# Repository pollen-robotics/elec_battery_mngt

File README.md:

# Battery-related Electronic Boards

This repository gathers several small PCBs for battery management. Including:

 - 2S BMS + USB-ish charger

## Basically
 - Designed with KiCAD 9.

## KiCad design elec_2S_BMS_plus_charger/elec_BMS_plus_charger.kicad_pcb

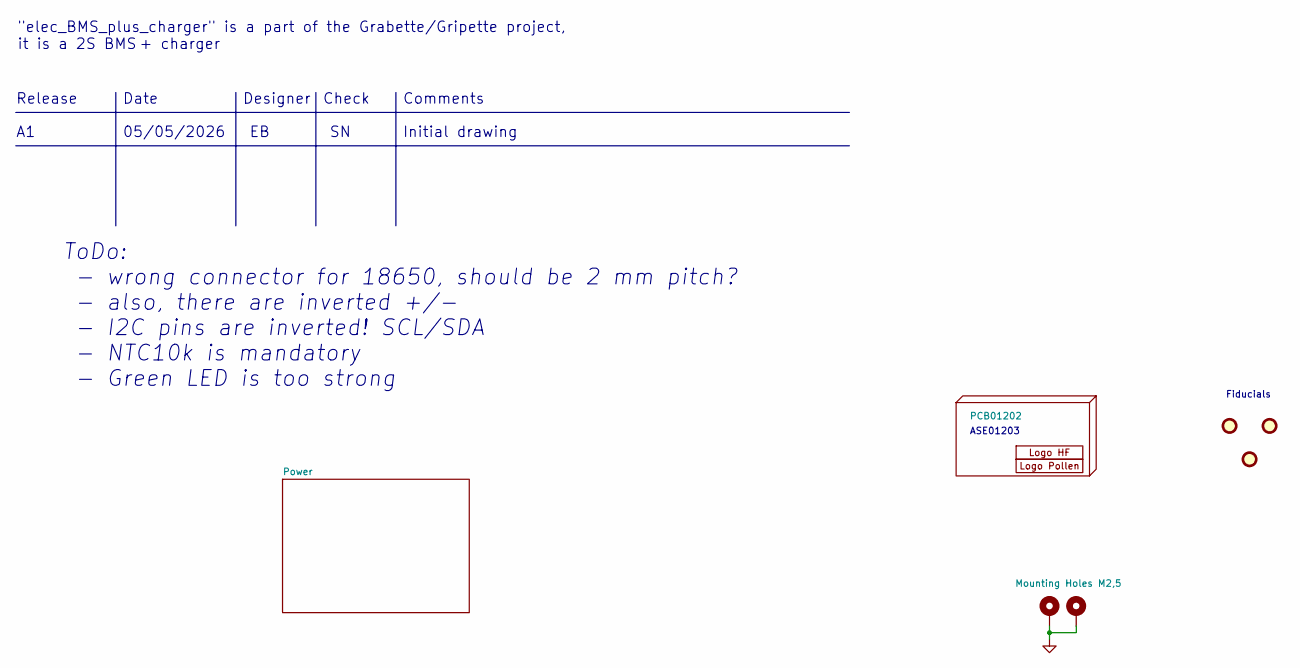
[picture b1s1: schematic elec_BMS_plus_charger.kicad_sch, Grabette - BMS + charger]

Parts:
FID1, FID2, FID3: DNP Fiducial; Fiducial_1mm_Mask2mm
H1: PCB01202
H2: Logo HF 2025; Logo_HF_2025
H3: DNP Logo Pollen 2021; Logo_Pollen_2021_sq
H4, H5: Mounting Holes M2,5; MountingHole_2.7mm_M2.5_ISO7380_Pad_TopBottom

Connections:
GND: H4.1, H5.1; also elsewhere on the board

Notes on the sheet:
Date
Check
Release
Fiducials
ASE01203
ToDo: - wrong connector for 18650, should be 2 mm pitch? - also, there are inverted +/- - I2C pins are inverted! SCL/SDA - NTC10k is mandatory - Green LED is too strong
Initial drawing
"elec_BMS_plus_charger" is a part of the Grabette/Gripette project, it is a 2S BMS + charger
Designer
Comments
05/05/2026

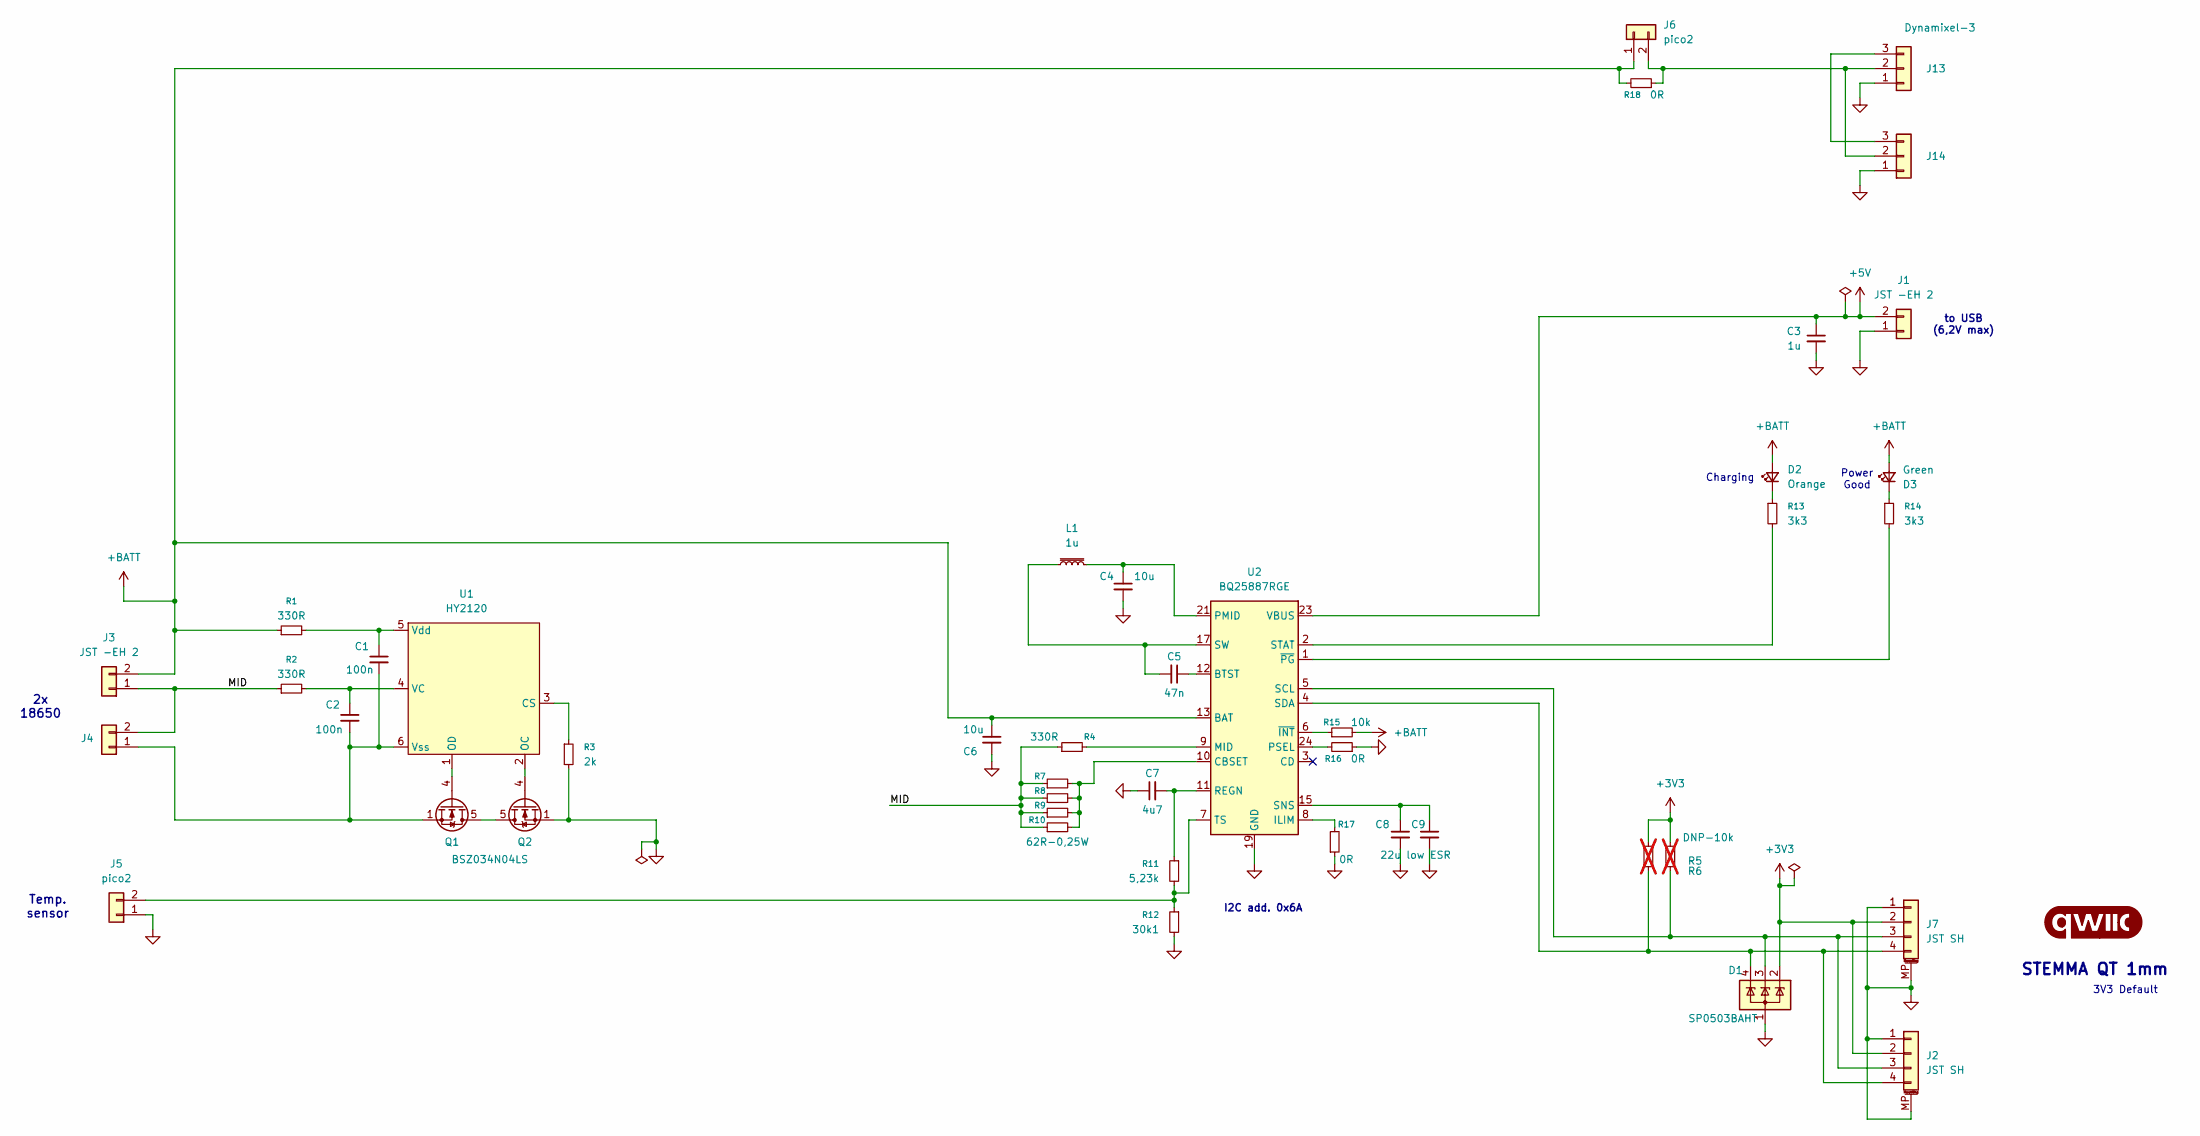
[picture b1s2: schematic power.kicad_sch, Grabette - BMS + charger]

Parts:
C1, C2: 100n; C_0402_1005Metric; LCSC Part C1525
C3: 1u; C_0402_1005Metric; LCSC Part C52923
C4, C6: 10u; C_0603_1608Metric; LCSC Part C19702
C5: 47n; C_0402_1005Metric; LCSC Part C272875
C7: 4u7; C_0603_1608Metric; LCSC Part C1705
C8, C9: 22u low ESR; C_0805_2012Metric; LCSC Part C5674
D1: SP0503BAHT; SOT-143; LCSC Part C41364459
D2: Orange; LED_0603_1608Metric; LCSC Part C84269
D3: Green; LED_0603_1608Metric; LCSC Part C19171301
G1: qwiic_Logo; Logo_qwiic_5mm
J1, J3, J4: JST -EH 2; JST_EH_B2B-EH-A_1x02_P2.50mm_Vertical; LCSC Part C160262
J2, J7: JST SH; JST_SH_BM04B-SRSS-TB_1x04-1MP_P1.00mm_Vertical; LCSC Part C160390
J5, J6: pico2; Molex_PicoBlade_53047-0210_1x02_P1.25mm_Vertical; LCSC Part C114130
J13, J14: Dynamixel-3; JST_EH_B3B-EH-A_1x03_P2.50mm_Vertical; LCSC Part C160259
L1: 1u; IND-SMD_L7.2-W6.6_GPSR0730; LCSC Part C5189744
Q1, Q2: BSZ034N04LS; PQFN_3.3x3.3mm_-_PG-TDSON-8_FL; LCSC Part C534652
R1, R2, R4: 330R; R_0402_1005Metric; LCSC Part C25104
R3: 2k; R_0402_1005Metric; LCSC Part C2909344
R5, R6: DNP-10k; R_0402_1005Metric; not fitted
R7, R8, R9, R10: 62R-0,25W; R_1206_3216Metric; LCSC Part C3013271
R11: 5,23k; R_0402_1005Metric; LCSC Part C2933105
R12: 30k1; R_0402_1005Metric; LCSC Part C2998131
R13, R14: 3k3; R_0402_1005Metric; LCSC Part C25890
R15: 10k; R_0402_1005Metric; LCSC Part C2906861
R16, R17: 0R; R_0402_1005Metric; LCSC Part C17168
R18: 0R; R_0603_1608Metric; LCSC Part C21189
U1: HY2120; SOT-23-6; LCSC Part C168778
U2: BQ25887RGE; Texas_RGE0024H_VQFN-24-1EP_4x4mm_P0.5mm_EP2.7x2.7mm; LCSC Part C2761614

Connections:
+3V3: D1.2 (K), J2.2, J7.2, R5.1, R6.1
+5V: C3.1, J1.2, U2.23 (VBUS)
+BATT: C6.1, D2.2 (A), D3.2 (A), J3.2, J6.1, R1.1, R15.2, R18.2, U2.13 (BAT), U2.14 (BAT)
/Power/MID: J3.1, J4.2, R2.1, R4.1, R7.1, R8.1, R9.1, R10.1
GND: C3.2, C4.2, C6.2, C7.1, C8.2, C9.2, D1.1 (A), J1.1, J2.1, J2.MP (MountPin), J5.1, J7.1, J7.MP (MountPin), J13.1, J14.1, Q2.1 (S), R3.2, R12.2, R16.1, R17.1, U2.19 (GND), U2.20 (GND), U2.25 (GND); also elsewhere on the board
unnamed: C4.1, L1.2, U2.21 (PMID), U2.22 (PMID)
unnamed: C5.2, L1.1, U2.17 (SW), U2.18 (SW)
unnamed: C8.1, C9.1, U2.15 (SNS), U2.16 (SNS)
unnamed: D2.1 (K), R13.1
unnamed: D3.1 (K), R14.1
unnamed: D1.3 (K), J2.3, J7.3, R5.2, U2.5 (SCL)
unnamed: D1.4 (K), J2.4, J7.4, R6.2, U2.4 (SDA)
unnamed: C1.2, C2.2, J4.1, Q1.1 (S), U1.6 (Vss)
unnamed: J5.2, R11.2, R12.1, U2.7 (TS)
unnamed: J6.2, J13.2, J14.2, R18.1
unnamed: J13.3, J14.3
unnamed: Q1.5 (D), Q2.5 (D)
unnamed: Q1.4 (G), U1.1 (OD)
unnamed: Q2.4 (G), U1.2 (OC)
unnamed: R3.1, U1.3 (CS)
unnamed: C2.1, R2.2, U1.4 (VC)
unnamed: C1.1, R1.2, U1.5 (Vdd)
unnamed: C5.1, U2.12 (BTST)
unnamed: R7.2, R8.2, R9.2, R10.2, U2.10 (CBSET)
unnamed: R17.2, U2.8 (ILIM)
unnamed: R4.2, U2.9 (MID)
unnamed: R16.2, U2.24 (PSEL)
unnamed: C7.2, R11.1, U2.11 (REGN)
unnamed: R13.2, U2.2 (STAT)
unnamed: R15.1, U2.6 (~INT)
unnamed: R14.2, U2.1 (~PG)

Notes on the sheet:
Power Good
to USB (6,2V max)
STEMMA QT 1mm
I2C add. 0x6A
Charging
2x 18650
Temp. sensor
3V3 Default

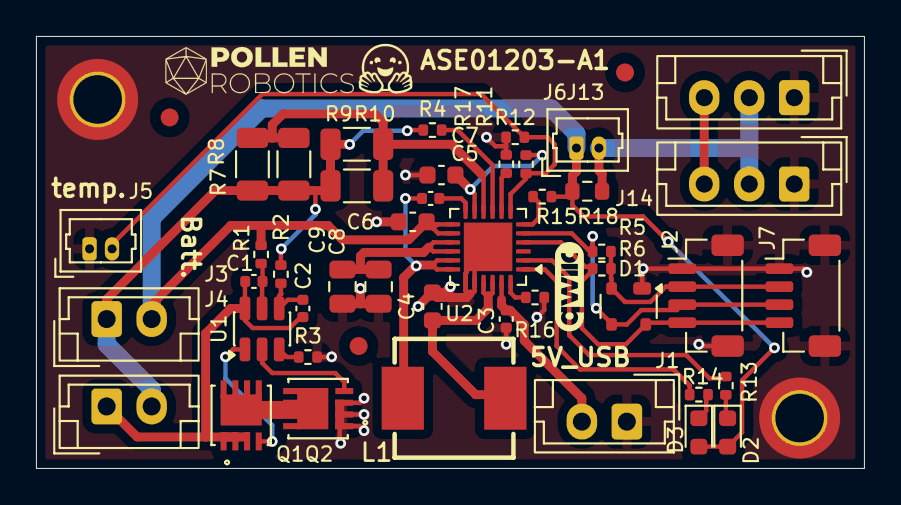
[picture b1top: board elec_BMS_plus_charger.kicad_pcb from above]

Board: 2 copper layers, 46.0 x 24.0 mm, 52 parts (0 on the bottom side), 31 nets.

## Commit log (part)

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2026-04-30 [init] Splitting projets and setting this repo for battery stuff.
2026-05-05 [update] Release A1, small batch of 15 @JLCPCB
2026-05-06 [added] Image
2026-05-06 [added] PNG
